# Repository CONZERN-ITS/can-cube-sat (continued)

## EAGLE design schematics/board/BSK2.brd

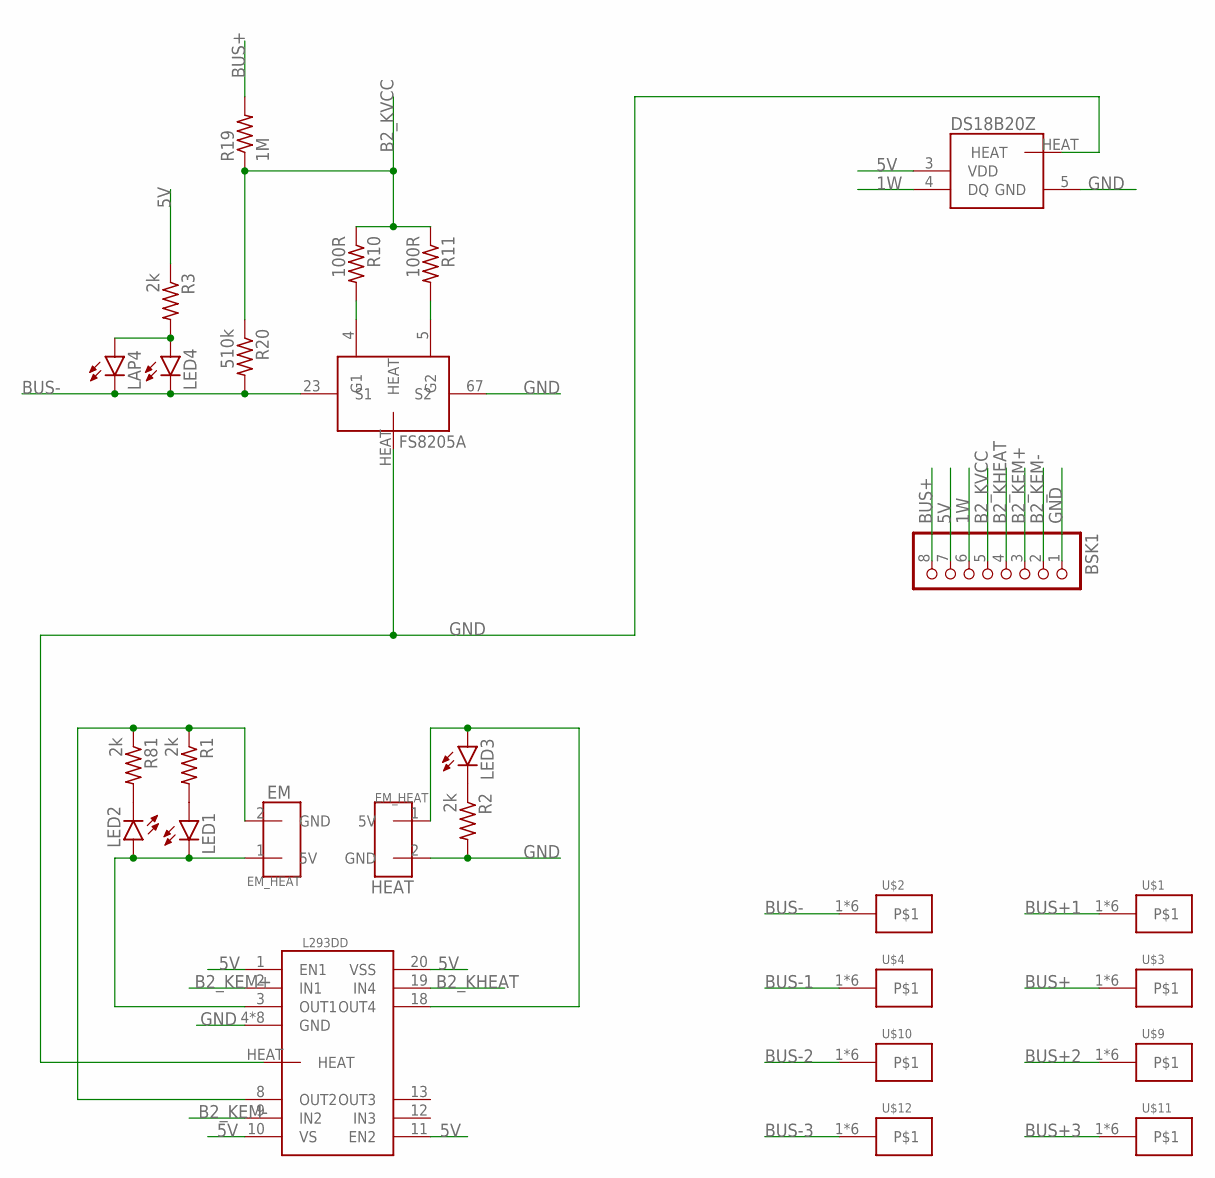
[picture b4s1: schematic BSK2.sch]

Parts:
BSK1: PINHD-1X8; 1X08
DS18B20Z: DS18B20Z
FS8205A: FS8205A+
L293DD: L293DD
LAP4: LAP4-BOTTOM; P47F-BOTTOM
LED1, LED2, LED3, LED4: LEDCHIPLED_0603; CHIPLED_0603
R1, R2, R3, R81: 2k; R0603
R10, R11: 100R; R0603
R19: 1M; R0603
R20: 510k; R0603
U$1, U$2, U$3, U$4, U$9, U$10, U$11, U$12: KCONNECT
U$6, U$7: EM_HEAT

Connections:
1W: BSK1.6, DS18B20Z.4 (DQ)
5V: BSK1.7, DS18B20Z.3 (VDD), L293DD.1 (EN1), L293DD.10 (VS), L293DD.11 (EN2), L293DD.20 (VSS), R3.1
B2_KEM+: BSK1.3, L293DD.2 (IN1)
B2_KEM-: BSK1.2, L293DD.9 (IN2)
B2_KHEAT: BSK1.4, L293DD.19 (IN4)
B2_KVCC: BSK1.5, R10.1, R11.1, R19.1, R20.1
BUS+: BSK1.8, R19.2, U$3.1, U$3.2, U$3.3, U$3.4, U$3.P$1, U$3.P$2
BUS+1: U$1.1, U$1.2, U$1.3, U$1.4, U$1.P$1, U$1.P$2
BUS+2: U$9.1, U$9.2, U$9.3, U$9.4, U$9.P$1, U$9.P$2
BUS+3: U$11.1, U$11.2, U$11.3, U$11.4, U$11.P$1, U$11.P$2
BUS-: FS8205A.23 (S1), LAP4.C, LED4.C, R20.2, U$2.1, U$2.2, U$2.3, U$2.4, U$2.P$1, U$2.P$2
BUS-1: U$4.1, U$4.2, U$4.3, U$4.4, U$4.P$1, U$4.P$2
BUS-2: U$10.1, U$10.2, U$10.3, U$10.4, U$10.P$1, U$10.P$2
BUS-3: U$12.1, U$12.2, U$12.3, U$12.4, U$12.P$1, U$12.P$2
GND: BSK1.1, DS18B20Z.5 (GND), DS18B20Z.HEAT, FS8205A.67 (S2), FS8205A.HEAT, L293DD.4 (GND), L293DD.5 (GND), L293DD.6 (GND), L293DD.7 (GND), L293DD.14 (GND), L293DD.15 (GND), L293DD.16 (GND), L293DD.17 (GND), L293DD.HEAT, R2.2, U$7.2 (GND)
unnamed: L293DD.3 (OUT1), LED1.C, LED2.A, U$6.1 (5V)
unnamed: L293DD.8 (OUT2), R1.1, R81.1, U$6.2 (GND)
unnamed: L293DD.18 (OUT4), LED3.A, U$7.1 (5V)
unnamed: FS8205A.4 (G1), R10.2
unnamed: FS8205A.5 (G2), R11.2
unnamed: LED2.C, R81.2
unnamed: LED1.A, R1.2
unnamed: LED3.C, R2.1
unnamed: LAP4.A, LED4.A, R3.2

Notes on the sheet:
HEAT

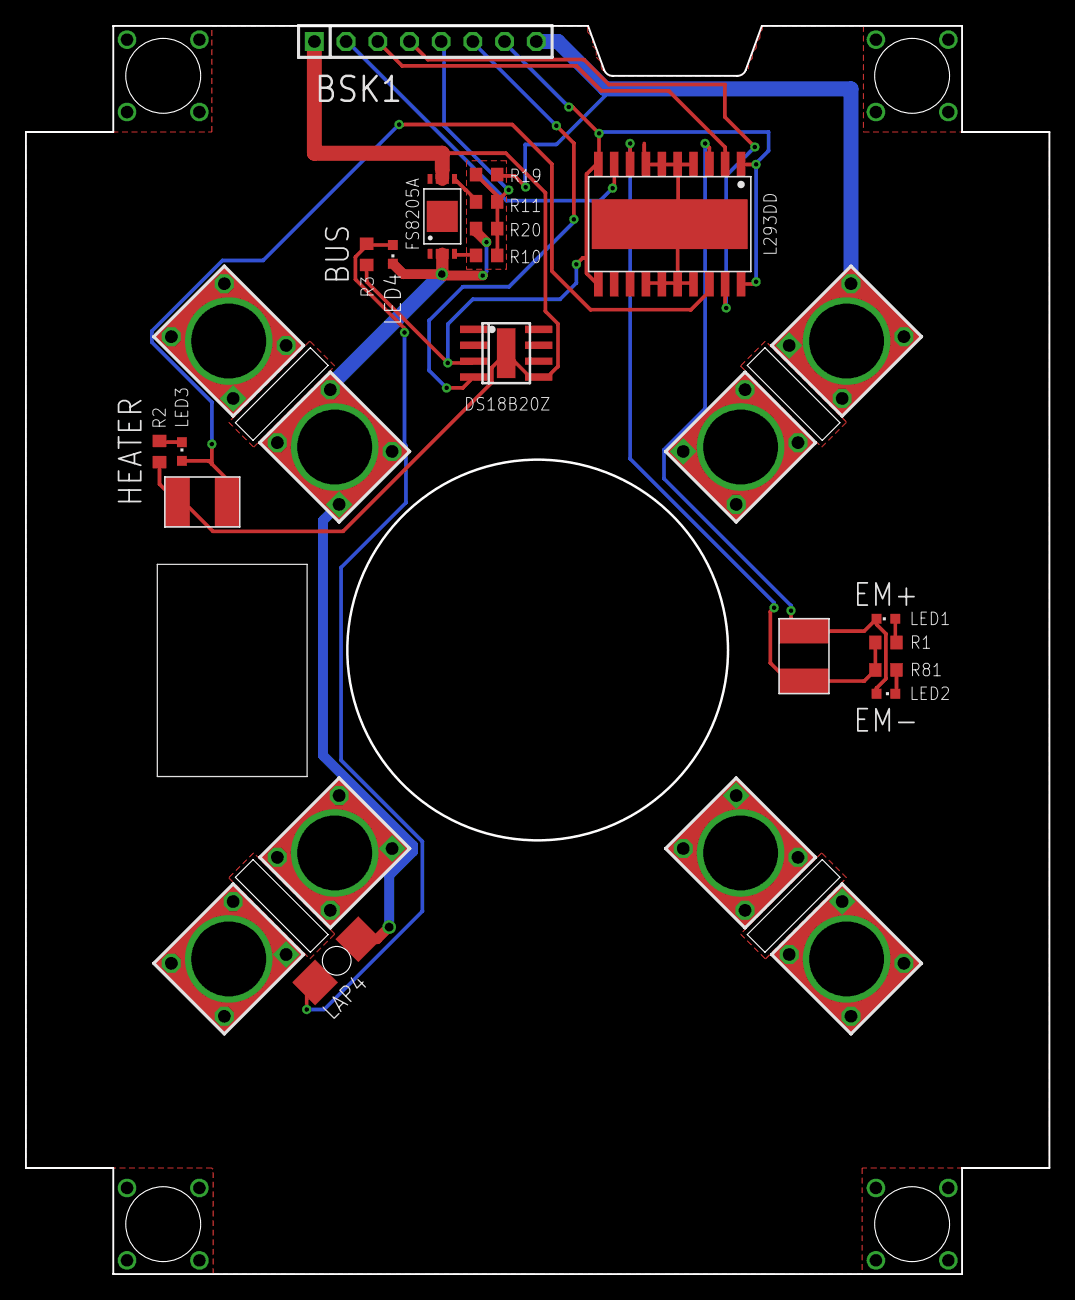
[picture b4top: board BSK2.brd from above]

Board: 2 copper layers, 82.0 x 100.0 mm, 27 parts (0 on the bottom side), 24 nets.

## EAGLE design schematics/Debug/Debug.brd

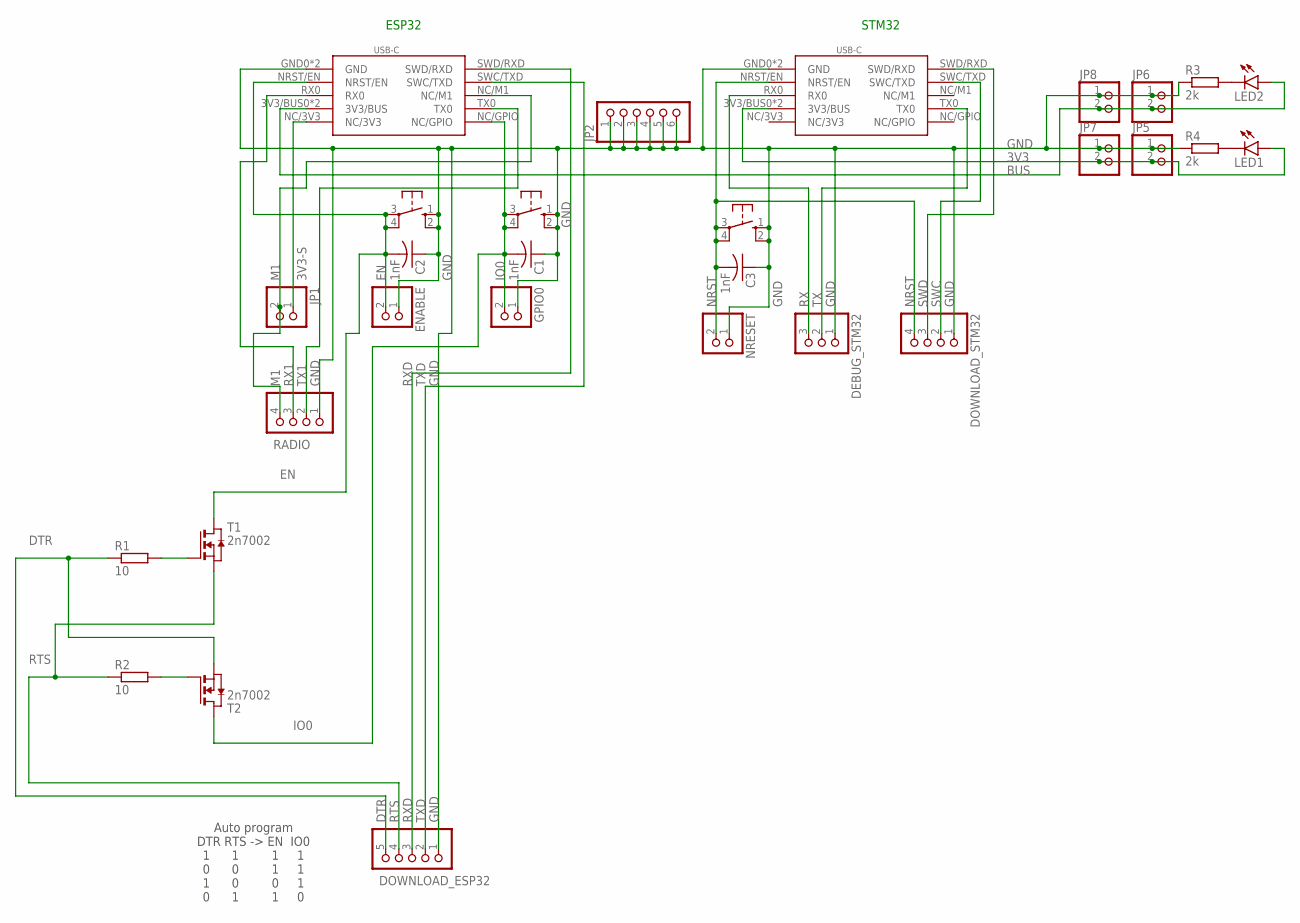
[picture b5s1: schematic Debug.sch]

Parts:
C1, C2, C3: 1nF; C0603
DEBUG_STM32: PINHD-1X3; 1X03
DOWNLOAD_ESP32: PINHD-1X5; 1X05
DOWNLOAD_STM32: PINHD-1X4; 1X04
EN: 10-XX; B3F-10XX
ENABLE: PINHD-1X2; 1X02
GPIO0: PINHD-1X2; 1X02
IO0: 10-XX; B3F-10XX
JP1, JP5, JP6, JP7, JP8: PINHD-1X2; 1X02
JP2: PINHD-1X6; 1X06
LED1, LED2: LEDCHIPLED_0603; CHIPLED_0603
NRESET: PINHD-1X2; 1X02
NRST: 10-XX; B3F-10XX
R1, R2: 10; R0603
R3, R4: 2k; R0603
RADIO: PINHD-1X4; 1X04
T1, T2: 2n7002; SOT-23
U$1, U$2: USB-C

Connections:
3V3: JP5.2, JP7.2, LED1.A, U$2.3V3/BUS0 (3V3/BUS), U$2.3V3/BUS1 (3V3/BUS)
3V3-S: JP1.1, U$1.NC/3V3
BUS: JP6.2, JP8.2, LED2.A, U$1.3V3/BUS0 (3V3/BUS), U$1.3V3/BUS1 (3V3/BUS)
DTR: DOWNLOAD_ESP32.5, R1.1, T2.2 (S)
EN: C2.2, EN.3, EN.4 (P1), ENABLE.2, T1.1 (D), U$1.NRST/EN
GND: C1.1, C2.1, C3.1, DEBUG_STM32.1, DOWNLOAD_ESP32.1, DOWNLOAD_STM32.1, EN.1 (S), EN.2 (S1), ENABLE.1, GPIO0.1, IO0.1 (S), IO0.2 (S1), JP2.1, JP2.2, JP2.3, JP2.4, JP2.5, JP2.6, JP5.1, JP6.1, JP7.1, JP8.1, NRESET.1, NRST.1 (S), NRST.2 (S1), R3.1, R4.1, RADIO.1, U$1.GND0 (GND), U$1.GND1 (GND), U$2.GND0 (GND), U$2.GND1 (GND)
IO0: C1.2, GPIO0.2, IO0.3, IO0.4 (P1), T2.1 (D), U$1.NC/GPIO
M1: JP1.2, RADIO.4, U$1.NC/M1
unnamed: R2.2, T2.3 (G)
unnamed: R1.2, T1.3 (G)
unnamed: LED1.C, R4.2
unnamed: LED2.C, R3.2
NRST: C3.2, DOWNLOAD_STM32.4, NRESET.2, NRST.3, NRST.4 (P1), U$2.NRST/EN
RTS: DOWNLOAD_ESP32.4, R2.1, T1.2 (S)
RX: DEBUG_STM32.3, U$2.RX0
RX1: RADIO.3, U$1.RX0
RXD: DOWNLOAD_ESP32.3, U$1.SWD/RXD
SWC: DOWNLOAD_STM32.2, U$2.SWC/TXD
SWD: DOWNLOAD_STM32.3, U$2.SWD/RXD
TX: DEBUG_STM32.2, U$2.TX0
TX1: RADIO.2, U$1.TX0
TXD: DOWNLOAD_ESP32.2, U$1.SWC/TXD

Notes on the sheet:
ESP32
STM32
Auto program DTR RTS -> EN IO0 1 1 1 1 0 0 1 1 1 0 0 1 0 1 1 0

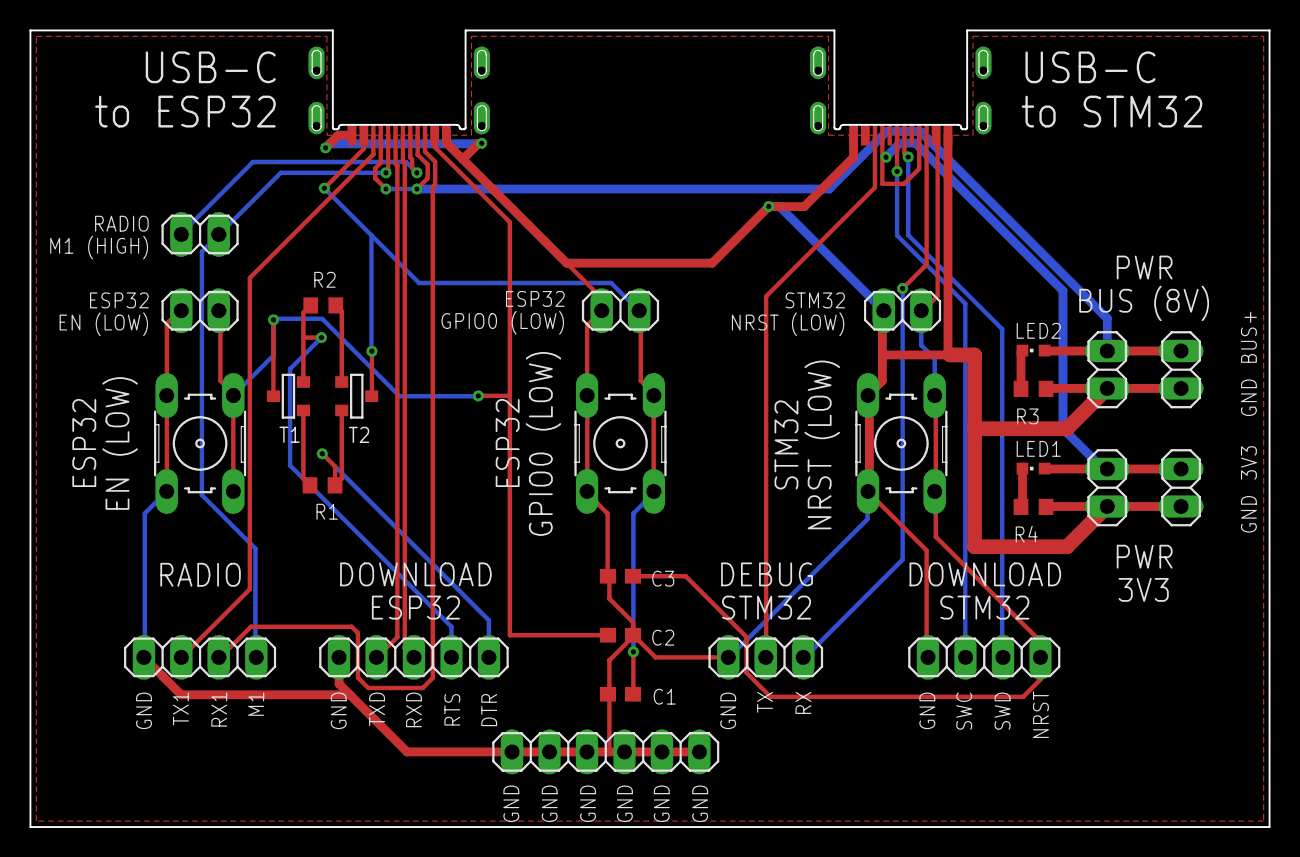
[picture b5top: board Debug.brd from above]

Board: 2 copper layers, 84.0 x 54.0 mm, 29 parts (0 on the bottom side), 22 nets.

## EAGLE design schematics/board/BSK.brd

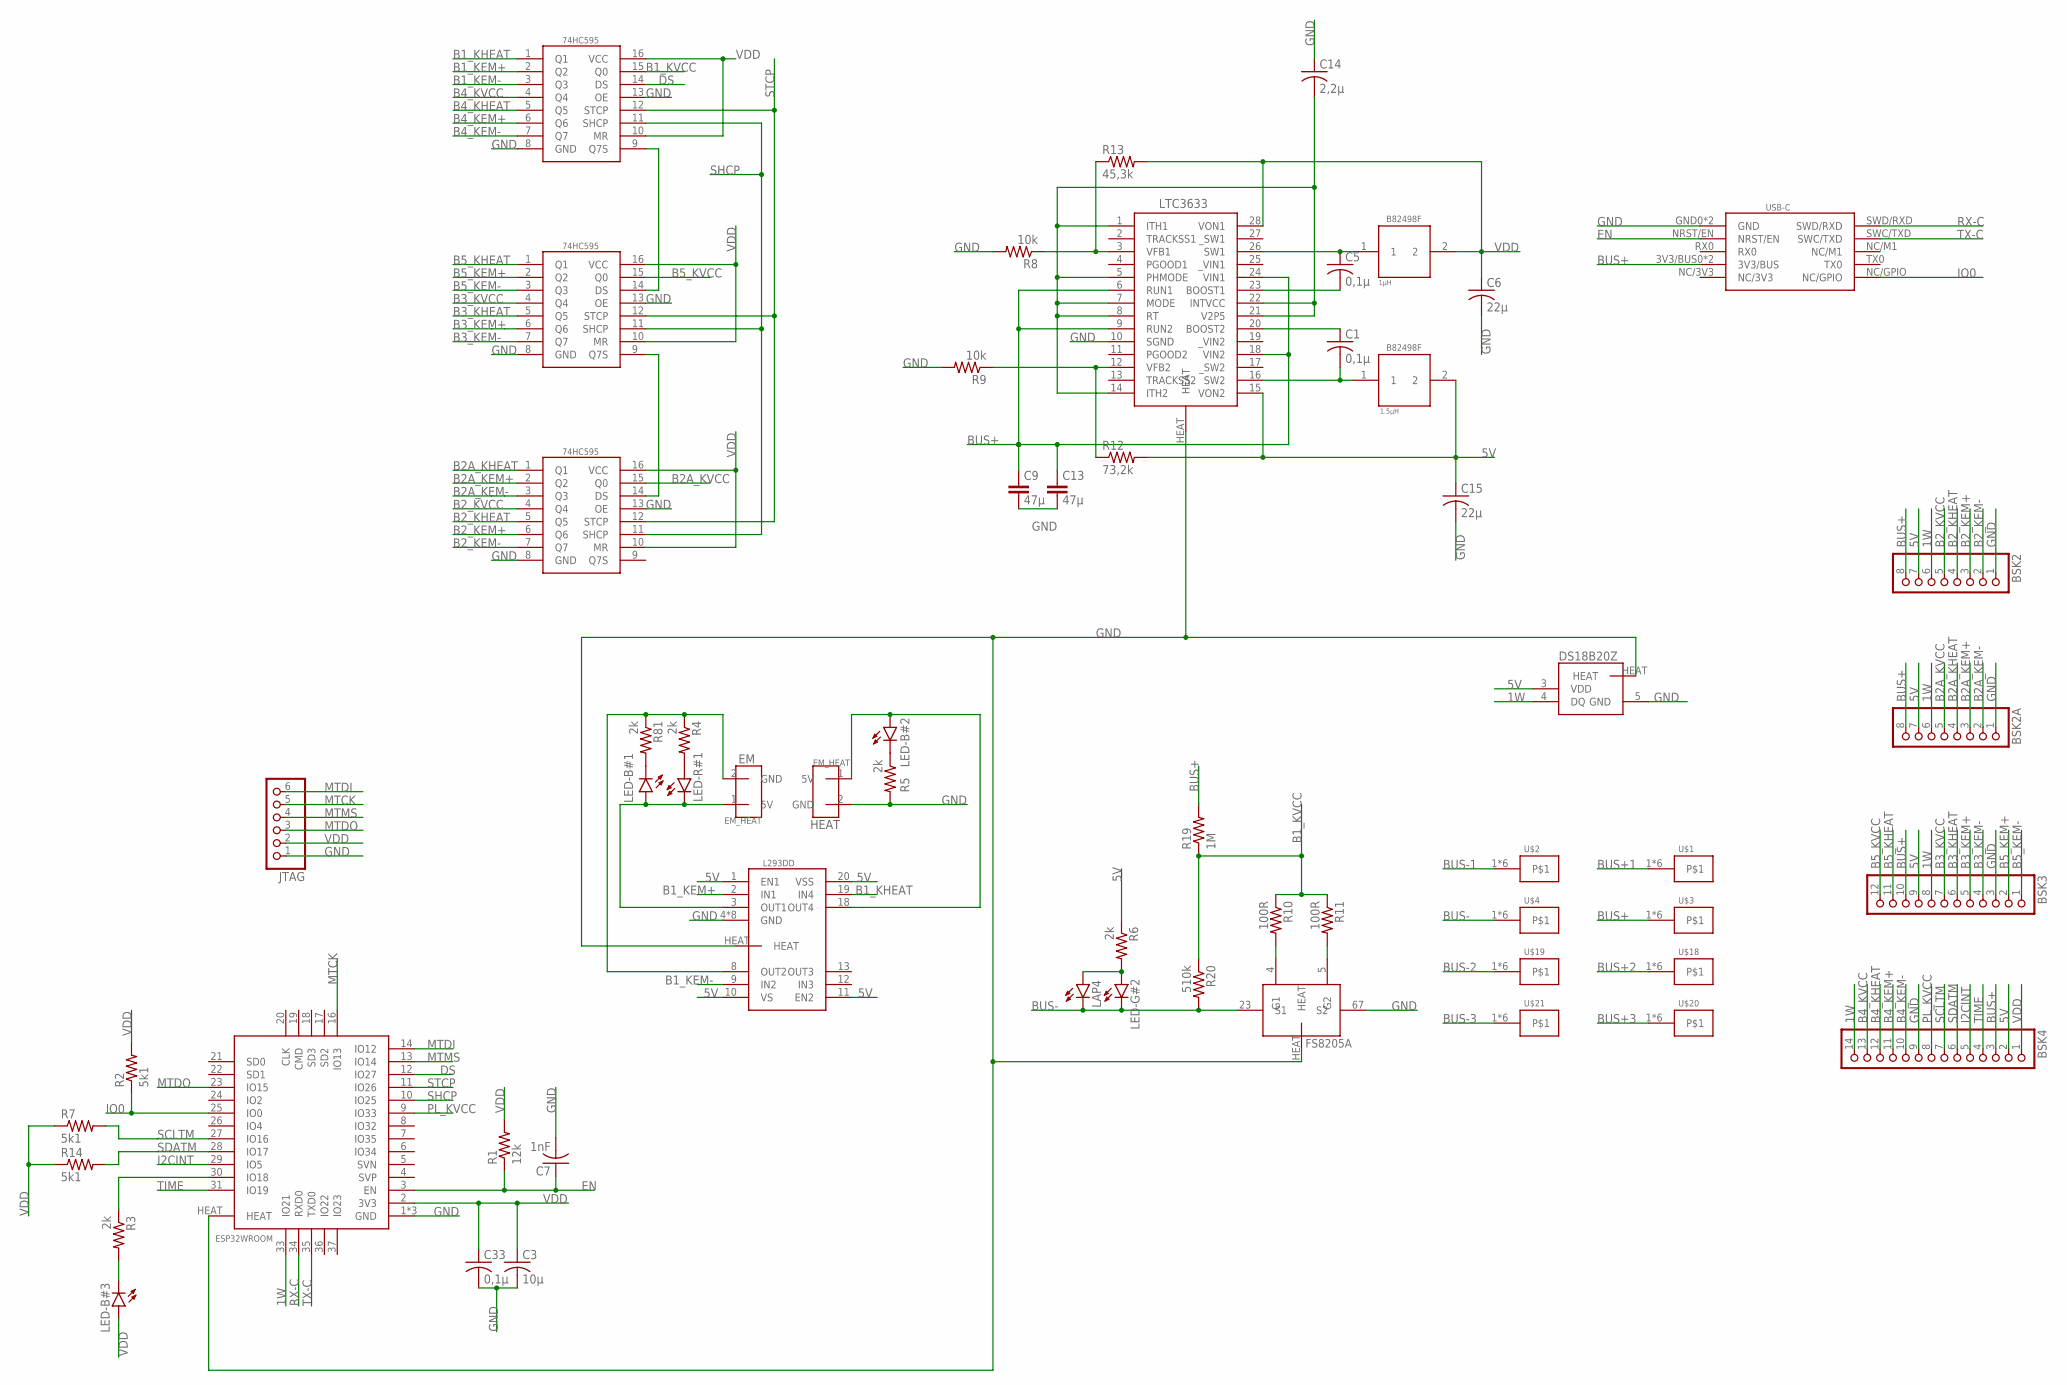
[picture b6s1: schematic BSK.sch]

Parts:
74HC595#1, 74HC595#2, 74HC595#3: 74HC595
B82498F#1: 1µH; B82498F
B82498F#2: B82498F
BSK2, BSK2A: PINHD-1X8; 1X08
BSK3: PINHD-1X12; 1X12
BSK4: PINHD-1X14; 1X14
C1, C5, C33: 0,1µ; C0603
C3: 10µ; C1206
C6, C15: 22µ; C1206
C7: 1nF; C0603
C9, C13: 47µ; C1210
C14: 2,2µ; C0603
DS18B20Z: DS18B20Z
EM: EM_HEAT
FS8205A: FS8205A+
HEATER: EM_HEAT
JTAG: PINHD-1X6; 1X06
L293DD: L293DD
LAP4: LAP4-BOTTOM; P47F-BOTTOM
LED-B#1, LED-B#2, LED-B#3: LEDCHIPLED_0603; CHIPLED_0603
LED-G#2: LEDCHIPLED_0603; CHIPLED_0603
LED-R#1: LEDCHIPLED_0603; CHIPLED_0603
LTC3633: LTC3633
R1: 12k; R0603
R2, R7, R14: 5k1; R0603
R3, R4, R5, R6, R81: 2k; R0603
R8, R9: 10k; R0603
R10, R11: 100R; R0603
R12: 73,2k; R0603
R13: 45,3k; R0603
R19: 1M; R0603
R20: 510k; R0603
U$1, U$2, U$3, U$4, U$18, U$19, U$20, U$21: KCONNECT
U$13: ESP32WROOM
USB-C: USB-C

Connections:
1W: BSK2.6, BSK2A.6, BSK3.8, BSK4.14, DS18B20Z.4 (DQ), U$13.33 (IO21)
5V: B82498F#2.2, BSK2.7, BSK2A.7, BSK3.9, BSK4.2, C15.1, DS18B20Z.3 (VDD), L293DD.1 (EN1), L293DD.10 (VS), L293DD.11 (EN2), L293DD.20 (VSS), LTC3633.15 (VON2), R6.1, R12.2
B1_KEM+: 74HC595#1.2 (Q2), L293DD.2 (IN1)
B1_KEM-: 74HC595#1.3 (Q3), L293DD.9 (IN2)
B1_KHEAT: 74HC595#1.1 (Q1), L293DD.19 (IN4)
B1_KVCC: 74HC595#1.15 (Q0), R10.1, R11.1, R19.1, R20.1
B2A_KEM+: 74HC595#3.2 (Q2), BSK2A.3
B2A_KEM-: 74HC595#3.3 (Q3), BSK2A.2
B2A_KHEAT: 74HC595#3.1 (Q1), BSK2A.4
B2A_KVCC: 74HC595#3.15 (Q0), BSK2A.5
B2_KEM+: 74HC595#3.6 (Q6), BSK2.3
B2_KEM-: 74HC595#3.7 (Q7), BSK2.2
B2_KHEAT: 74HC595#3.5 (Q5), BSK2.4
B2_KVCC: 74HC595#3.4 (Q4), BSK2.5
B3_KEM+: 74HC595#2.6 (Q6), BSK3.5
B3_KEM-: 74HC595#2.7 (Q7), BSK3.4
B3_KHEAT: 74HC595#2.5 (Q5), BSK3.6
B3_KVCC: 74HC595#2.4 (Q4), BSK3.7
B4_KEM+: 74HC595#1.6 (Q6), BSK4.11
B4_KEM-: 74HC595#1.7 (Q7), BSK4.10
B4_KHEAT: 74HC595#1.5 (Q5), BSK4.12
B4_KVCC: 74HC595#1.4 (Q4), BSK4.13
B5_KEM+: 74HC595#2.2 (Q2), BSK3.2
B5_KEM-: 74HC595#2.3 (Q3), BSK3.1
B5_KHEAT: 74HC595#2.1 (Q1), BSK3.11
B5_KVCC: 74HC595#2.15 (Q0), BSK3.12
BUS+: BSK2.8, BSK2A.8, BSK3.10, BSK4.3, C9.1, C13.1, LTC3633.6 (RUN1), LTC3633.9 (RUN2), LTC3633.18 (VIN2), LTC3633.24 (VIN1), R19.2, U$3.1, U$3.2, U$3.3, U$3.4, U$3.P$1, U$3.P$2, USB-C.3V3/BUS0 (3V3/BUS), USB-C.3V3/BUS1 (3V3/BUS)
BUS+1: U$1.1, U$1.2, U$1.3, U$1.4, U$1.P$1, U$1.P$2
BUS+2: U$18.1, U$18.2, U$18.3, U$18.4, U$18.P$1, U$18.P$2
BUS+3: U$20.1, U$20.2, U$20.3, U$20.4, U$20.P$1, U$20.P$2
BUS-: FS8205A.23 (S1), LAP4.C, LED-G#2.C, R20.2, U$4.1, U$4.2, U$4.3, U$4.4, U$4.P$1, U$4.P$2
BUS-1: U$2.1, U$2.2, U$2.3, U$2.4, U$2.P$1, U$2.P$2
BUS-2: U$19.1, U$19.2, U$19.3, U$19.4, U$19.P$1, U$19.P$2
BUS-3: U$21.1, U$21.2, U$21.3, U$21.4, U$21.P$1, U$21.P$2
DS: 74HC595#1.14 (DS), U$13.12 (IO27)
EN: C7.1, R1.1, U$13.3 (EN), USB-C.NRST/EN
GND: 74HC595#1.8 (GND), 74HC595#1.13 (OE), 74HC595#2.8 (GND), 74HC595#2.13 (OE), 74HC595#3.8 (GND), 74HC595#3.13 (OE), BSK2.1, BSK2A.1, BSK3.3, BSK4.9, C3.2, C6.2, C7.2, C9.2, C13.2, C14.1, C15.2, C33.2, DS18B20Z.5 (GND), DS18B20Z.HEAT, FS8205A.67 (S2), FS8205A.HEAT, HEATER.2 (GND), JTAG.1, L293DD.4 (GND), L293DD.5 (GND), L293DD.6 (GND), L293DD.7 (GND), L293DD.14 (GND), L293DD.15 (GND), L293DD.16 (GND), L293DD.17 (GND), L293DD.HEAT, LTC3633.10 (SGND), LTC3633.HEAT, R5.2, R8.2, R9.2, U$13.1 (GND), U$13.15 (GND), U$13.38 (GND), U$13.HEAT, USB-C.GND0 (GND), USB-C.GND1 (GND)
I2CINT: BSK4.5, U$13.29 (IO5)
IO0: R2.1, U$13.25 (IO0), USB-C.NC/GPIO
IO1: R3.1, U$13.30 (IO18)
MTCK: JTAG.5, U$13.16 (IO13)
MTDI: JTAG.6, U$13.14 (IO12)
MTDO: JTAG.3, U$13.23 (IO15)
MTMS: JTAG.4, U$13.13 (IO14)
unnamed: EM.1 (5V), L293DD.3 (OUT1), LED-B#1.A, LED-R#1.C
unnamed: EM.2 (GND), L293DD.8 (OUT2), R4.1, R81.1
unnamed: HEATER.1 (5V), L293DD.18 (OUT4), LED-B#2.A
unnamed: FS8205A.4 (G1), R10.2
unnamed: FS8205A.5 (G2), R11.2
unnamed: 74HC595#1.9 (Q7S), 74HC595#2.14 (DS)
unnamed: 74HC595#2.9 (Q7S), 74HC595#3.14 (DS)
unnamed: C14.2, LTC3633.1 (ITH1), LTC3633.5 (PHMODE), LTC3633.7 (MODE), LTC3633.8 (RT), LTC3633.14 (ITH2), LTC3633.21 (V2P5), LTC3633.22 (INTVCC)
unnamed: LTC3633.3 (VFB1), R8.1, R13.1
unnamed: B82498F#1.1, C5.1, LTC3633.26 (SW1)
unnamed: C5.2, LTC3633.23 (BOOST1)
unnamed: C1.1, LTC3633.20 (BOOST2)
unnamed: B82498F#2.1, C1.2, LTC3633.16 (SW2)
unnamed: LED-B#3.C, R3.2
unnamed: LED-B#1.C, R81.2
unnamed: LED-R#1.A, R4.2
unnamed: LED-B#2.C, R5.1
unnamed: LAP4.A, LED-G#2.A, R6.2
unnamed: LTC3633.12 (VFB2), R9.1, R12.1
PL_KVCC: BSK4.8, U$13.9 (IO33)
RX-C: U$13.34 (RXD0), USB-C.SWD/RXD
SCLTM: BSK4.7, R7.2, U$13.27 (IO16)
SDATM: BSK4.6, R14.2, U$13.28 (IO17)
SHCP: 74HC595#1.11 (SHCP), 74HC595#2.11 (SHCP), 74HC595#3.11 (SHCP), U$13.10 (IO25)
STCP: 74HC595#1.12 (STCP), 74HC595#2.12 (STCP), 74HC595#3.12 (STCP), U$13.11 (IO26)
TIME: BSK4.4, U$13.31 (IO19)
TX-C: U$13.35 (TXD0), USB-C.SWC/TXD
VDD: 74HC595#1.10 (MR), 74HC595#1.16 (VCC), 74HC595#2.10 (MR), 74HC595#2.16 (VCC), 74HC595#3.10 (MR), 74HC595#3.16 (VCC), B82498F#1.2, BSK4.1, C3.1, C6.1, C33.1, JTAG.2, LED-B#3.A, LTC3633.28 (VON1), R1.2, R2.2, R7.1, R13.2, R14.1, U$13.2 (3V3)

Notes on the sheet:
HEAT
1µH
1.5µH

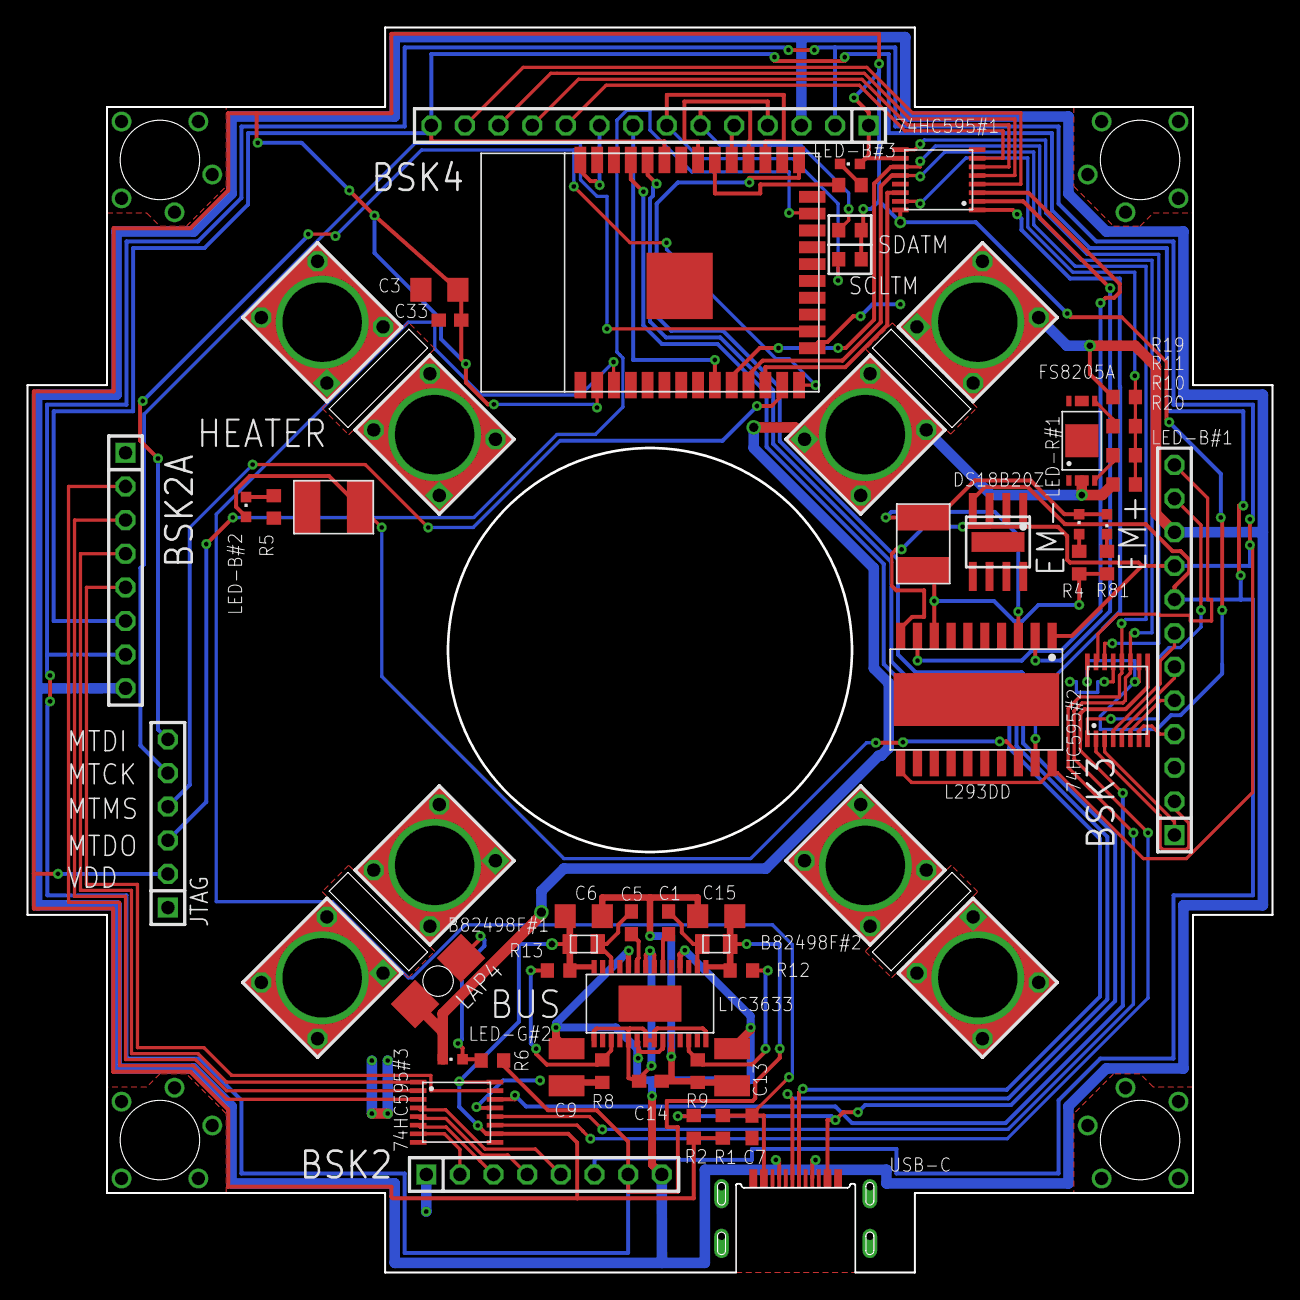
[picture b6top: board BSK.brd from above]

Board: 2 copper layers, 94.0 x 94.0 mm, 59 parts (0 on the bottom side), 72 nets.

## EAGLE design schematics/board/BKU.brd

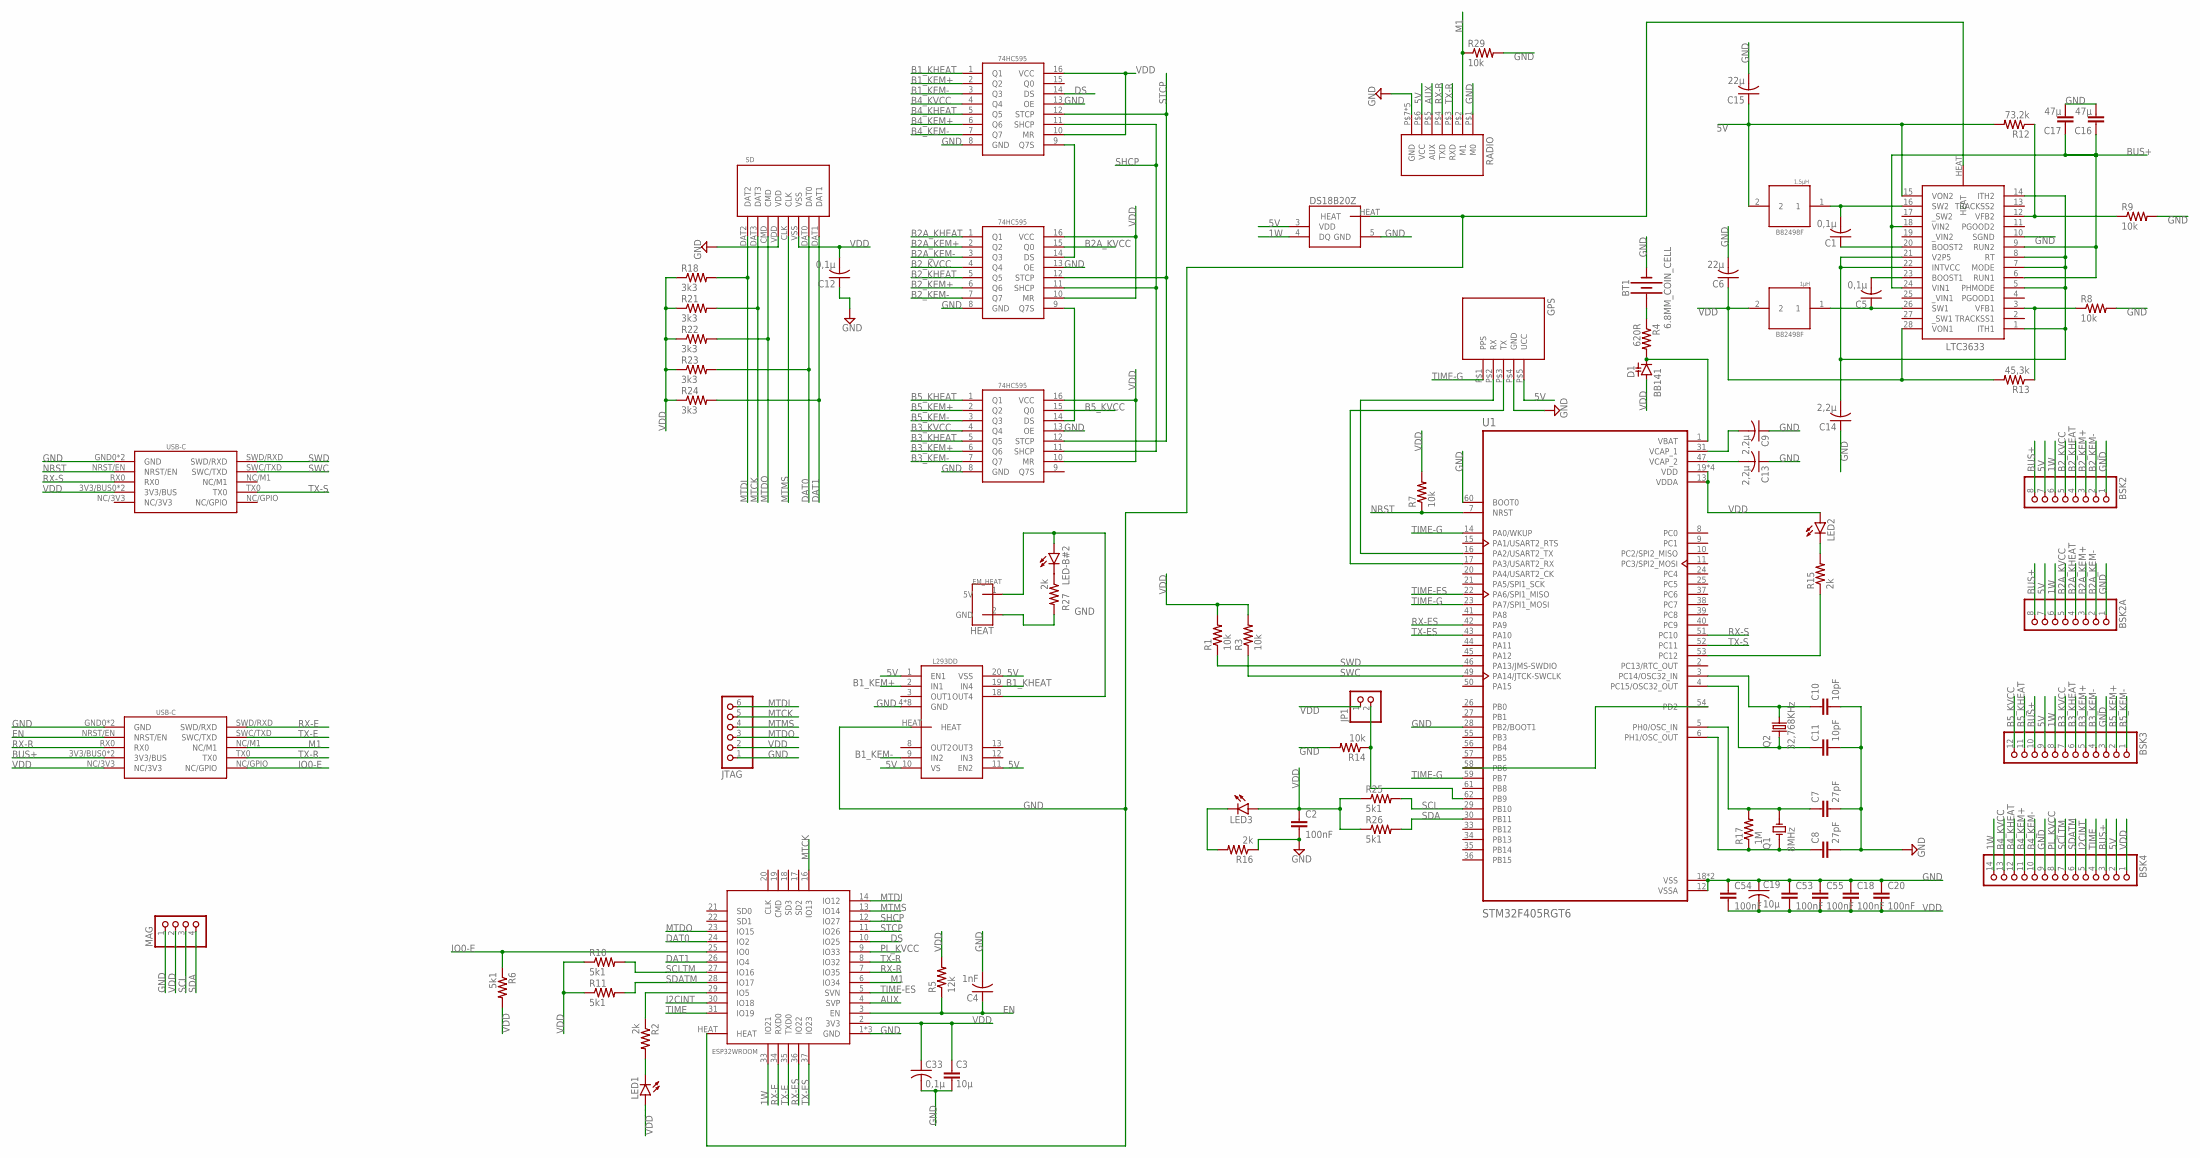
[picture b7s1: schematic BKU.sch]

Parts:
BSK2, BSK2A: PINHD-1X8; 1X08
BSK3: PINHD-1X12; 1X12
BSK4: PINHD-1X14; 1X14
BT1: 6.8MM_COIN_CELL; BATTCON-6.8MM
C1, C5, C12, C33: 0,1µ; C0603
C2, C18, C20, C53, C54, C55: 100nF; C0603
C3, C19: 10µ; C1206
C4: 1nF; C0603
C6, C15: 22µ; C1206
C7, C8: 27pF; C0603
C9, C13, C14: 2,2µ; C0603
C10, C11: 10pF; C0603
C16, C17: 47µ; C1210
D1: BB141; SOD523
GPS: GPSNEO6M; GPS-NEO6M
JP1: PINHD-1X2; 1X02
JTAG: PINHD-1X6; 1X06
LED1, LED2, LED3: LEDCHIPLED_0603; CHIPLED_0603
LED-B#2: LEDCHIPLED_0603; CHIPLED_0603
MAG: PINHD-1X4; 1X04
Q1: 8MHz; XTAL_9C-8.000MEEJ-T
Q2: 32,768KHz; C005R
R1, R3, R7, R8, R9, R14, R29: 10k; R0603
R2, R15, R16, R27: 2k; R0603
R4: 620R; R0603
R5: 12k; R0603
R6, R10, R11, R25, R26: 5k1; R0603
R12: 73,2k; R0603
R13: 45,3k; R0603
R17: 1M; R0603
R18, R21, R22, R23, R24: 3k3; R0603
RADIO: RADIO
SD: SD
U1: STM32F405RGT6; QFP50P1200X1200X160-64N
U$4, U$6: USB-C
U$5: DS18B20Z
U$7: EM_HEAT
U$8: L293DD
U$10: LTC3633
U$11: 1µH; B82498F
U$12: B82498F
U$13: ESP32WROOM
U$18, U$19, U$20: 74HC595

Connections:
1W: BSK2.6, BSK2A.6, BSK3.8, BSK4.14, U$5.4 (DQ), U$13.33 (IO21)
5V: BSK2.7, BSK2A.7, BSK3.9, BSK4.2, C15.1, GPS.P$5 (UCC), R12.2, RADIO.P$6 (VCC), U$5.3 (VDD), U$8.1 (EN1), U$8.10 (VS), U$8.11 (EN2), U$8.20 (VSS), U$10.15 (VON2), U$12.2
AUX: RADIO.P$5 (AUX), U$13.4 (SVP)
B1_KEM+: U$8.2 (IN1), U$18.2 (Q2)
B1_KEM-: U$8.9 (IN2), U$18.3 (Q3)
B1_KHEAT: U$8.19 (IN4), U$18.1 (Q1)
B2A_KEM+: BSK2A.3, U$19.2 (Q2)
B2A_KEM-: BSK2A.2, U$19.3 (Q3)
B2A_KHEAT: BSK2A.4, U$19.1 (Q1)
B2A_KVCC: BSK2A.5, U$19.15 (Q0)
B2_KEM+: BSK2.3, U$19.6 (Q6)
B2_KEM-: BSK2.2, U$19.7 (Q7)
B2_KHEAT: BSK2.4, U$19.5 (Q5)
B2_KVCC: BSK2.5, U$19.4 (Q4)
B3_KEM+: BSK3.5, U$20.6 (Q6)
B3_KEM-: BSK3.4, U$20.7 (Q7)
B3_KHEAT: BSK3.6, U$20.5 (Q5)
B3_KVCC: BSK3.7, U$20.4 (Q4)
B4_KEM+: BSK4.11, U$18.6 (Q6)
B4_KEM-: BSK4.10, U$18.7 (Q7)
B4_KHEAT: BSK4.12, U$18.5 (Q5)
B4_KVCC: BSK4.13, U$18.4 (Q4)
B5_KEM+: BSK3.2, U$20.2 (Q2)
B5_KEM-: BSK3.1, U$20.3 (Q3)
B5_KHEAT: BSK3.11, U$20.1 (Q1)
B5_KVCC: BSK3.12, U$20.15 (Q0)
BUS+: BSK2.8, BSK2A.8, BSK3.10, BSK4.3, C16.1, C17.1, U$6.3V3/BUS0 (3V3/BUS), U$6.3V3/BUS1 (3V3/BUS), U$10.6 (RUN1), U$10.9 (RUN2), U$10.18 (VIN2), U$10.24 (VIN1)
DAT0: R23.2, SD.DAT0, U$13.24 (IO2)
DAT1: R24.2, SD.DAT1, U$13.26 (IO4)
DS: U$13.10 (IO25), U$18.14 (DS)
EN: C4.1, R5.1, U$6.NRST/EN, U$13.3 (EN)
GND: BSK2.1, BSK2A.1, BSK3.3, BSK4.9, BT1.-, C2.2, C3.2, C4.2, C6.2, C7.2, C8.2, C9.1, C10.2, C11.2, C12.1, C13.1, C14.1, C15.2, C16.2, C17.2, C18.1, C19.1, C20.1, C33.2, C53.1, C54.1, C55.1, GPS.P$4 (GND), JTAG.1, MAG.1, R8.2, R9.2, R14.2, R16.1, R27.2, R29.2, RADIO.P$1 (M0), RADIO.P$7 (GND), RADIO.P$9 (GND), RADIO.P$15 (GND), RADIO.P$16 (GND), RADIO.P$17 (GND), SD.VDD, U1.12 (VSSA), U1.18 (VSS), U1.28 (PB2/BOOT1), U1.60 (BOOT0), U1.63 (VSS), U$4.GND0 (GND), U$4.GND1 (GND), U$5.5 (GND), U$5.HEAT, U$6.GND0 (GND), U$6.GND1 (GND), U$7.2 (GND), U$8.4 (GND), U$8.5 (GND), U$8.6 (GND), U$8.7 (GND), U$8.14 (GND), U$8.15 (GND), U$8.16 (GND), U$8.17 (GND), U$8.HEAT, U$10.10 (SGND), U$10.HEAT, U$13.1 (GND), U$13.15 (GND), U$13.38 (GND), U$13.HEAT, U$18.8 (GND), U$18.13 (OE), U$19.8 (GND), U$19.13 (OE), U$20.8 (GND), U$20.13 (OE)
I2CINT: BSK4.5, U$13.30 (IO18)
IO0-E: R6.1, U$6.NC/GPIO, U$13.25 (IO0)
IO1: R2.1, U$13.29 (IO5)
M1: R29.1, RADIO.P$2 (M1), U$6.NC/M1, U$13.6 (IO34)
MTCK: JTAG.5, R21.2, SD.DAT3, U$13.16 (IO13)
MTDI: JTAG.6, R18.2, SD.DAT2, U$13.14 (IO12)
MTDO: JTAG.3, R22.2, SD.CMD, U$13.23 (IO15)
MTMS: JTAG.4, SD.CLK, U$13.13 (IO14)
unnamed: BT1.+, R4.1
unnamed: D1.C, R4.2, U1.1 (VBAT)
unnamed: LED-B#2.A, U$7.1 (5V), U$8.18 (OUT4)
unnamed: LED1.C, R2.2
unnamed: JP1.2, R14.1, U1.62 (PB9)
unnamed: U1.54 (PD2), U1.58 (PB6)
unnamed: C9.2, U1.31 (VCAP_1)
unnamed: C13.2, U1.47 (VCAP_2)
unnamed: C8.1, Q1.1, R17.1, U1.6 (PH1/OSC_OUT)
unnamed: U$18.9 (Q7S), U$19.14 (DS)
unnamed: U$19.9 (Q7S), U$20.14 (DS)
unnamed: C14.2, U$10.1 (ITH1), U$10.5 (PHMODE), U$10.7 (MODE), U$10.8 (RT), U$10.14 (ITH2), U$10.21 (V2P5), U$10.22 (INTVCC)
unnamed: R8.1, R13.1, U$10.3 (VFB1)
unnamed: C5.1, U$10.26 (SW1), U$11.1
unnamed: C7.1, Q1.2, R17.2, U1.5 (PH0/OSC_IN)
unnamed: C5.2, U$10.23 (BOOST1)
unnamed: C1.1, U$10.20 (BOOST2)
unnamed: C1.2, U$10.16 (SW2), U$12.1
unnamed: C10.1, Q2.P$2 (2), U1.3 (PC14/OSC32_IN)
unnamed: C11.1, Q2.P$1 (1), U1.4 (PC15/OSC32_OUT)
unnamed: LED2.C, R15.2
unnamed: R15.1, U1.53 (PC12)
unnamed: R9.1, R12.1, U$10.12 (VFB2)
unnamed: LED3.C, R16.2
unnamed: GPS.P$2 (RX), U1.16 (PA2/USART2_TX)
unnamed: GPS.P$3 (TX), U1.17 (PA3/USART2_RX)
unnamed: LED-B#2.C, R27.1
NRST: R7.1, U1.7 (NRST), U$4.NRST/EN
PL_KVCC: BSK4.8, U$13.9 (IO33)
RX-E: U$6.SWD/RXD, U$13.34 (RXD0)
RX-ES: U1.42 (PA9), U$13.36 (IO22)
RX-R: RADIO.P$4 (TXD), U$6.RX0, U$13.7 (IO35)
RX-S: U1.51 (PC10), U$4.RX0
SCL: MAG.3, R25.2, U1.29 (PB10)
SCLTM: BSK4.7, R10.2, U$13.27 (IO16)
SDA: MAG.4, R26.2, U1.30 (PB11)
SDATM: BSK4.6, R11.2, U$13.28 (IO17)
SHCP: U$13.12 (IO27), U$18.11 (SHCP), U$19.11 (SHCP), U$20.11 (SHCP)
STCP: U$13.11 (IO26), U$18.12 (STCP), U$19.12 (STCP), U$20.12 (STCP)
SWC: R3.1, U1.49 (PA14/JTCK-SWCLK), U$4.SWC/TXD
SWD: R1.1, U1.46 (PA13/JMS-SWDIO), U$4.SWD/RXD
TIME: BSK4.4, U$13.31 (IO19)
TIME-ES: U1.22 (PA6/SPI1_MISO), U$13.5 (SVN)
TIME-G: GPS.P$1 (PPS), U1.14 (PA0/WKUP), U1.23 (PA7/SPI1_MOSI), U1.59 (PB7)
TX-E: U$6.SWC/TXD, U$13.35 (TXD0)
TX-ES: U1.43 (PA10), U$13.37 (IO23)
TX-R: RADIO.P$3 (RXD), U$6.TX0, U$13.8 (IO32)
TX-S: U1.52 (PC11), U$4.TX0
VDD: BSK4.1, C2.1, C3.1, C6.1, C12.2, C18.2, C19.2, C20.2, C33.1, C53.2, C54.2, C55.2, D1.A, JP1.1, JTAG.2, LED1.A, LED2.A, LED3.A, MAG.2, R1.2, R3.2, R5.2, R6.2, R7.2, R10.1, R11.1, R13.2, R18.1, R21.1, R22.1, R23.1, R24.1, R25.1, R26.1, SD.VSS, U1.13 (VDDA), U1.19 (VDD), U1.32 (VDD), U1.48 (VDD), U1.64 (VDD), U$4.3V3/BUS0 (3V3/BUS), U$4.3V3/BUS1 (3V3/BUS), U$6.NC/3V3, U$10.28 (VON1), U$11.2, U$13.2 (3V3), U$18.10 (MR), U$18.16 (VCC), U$19.10 (MR), U$19.16 (VCC), U$20.10 (MR), U$20.16 (VCC)

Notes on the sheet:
HEAT
1µH
1.5µH

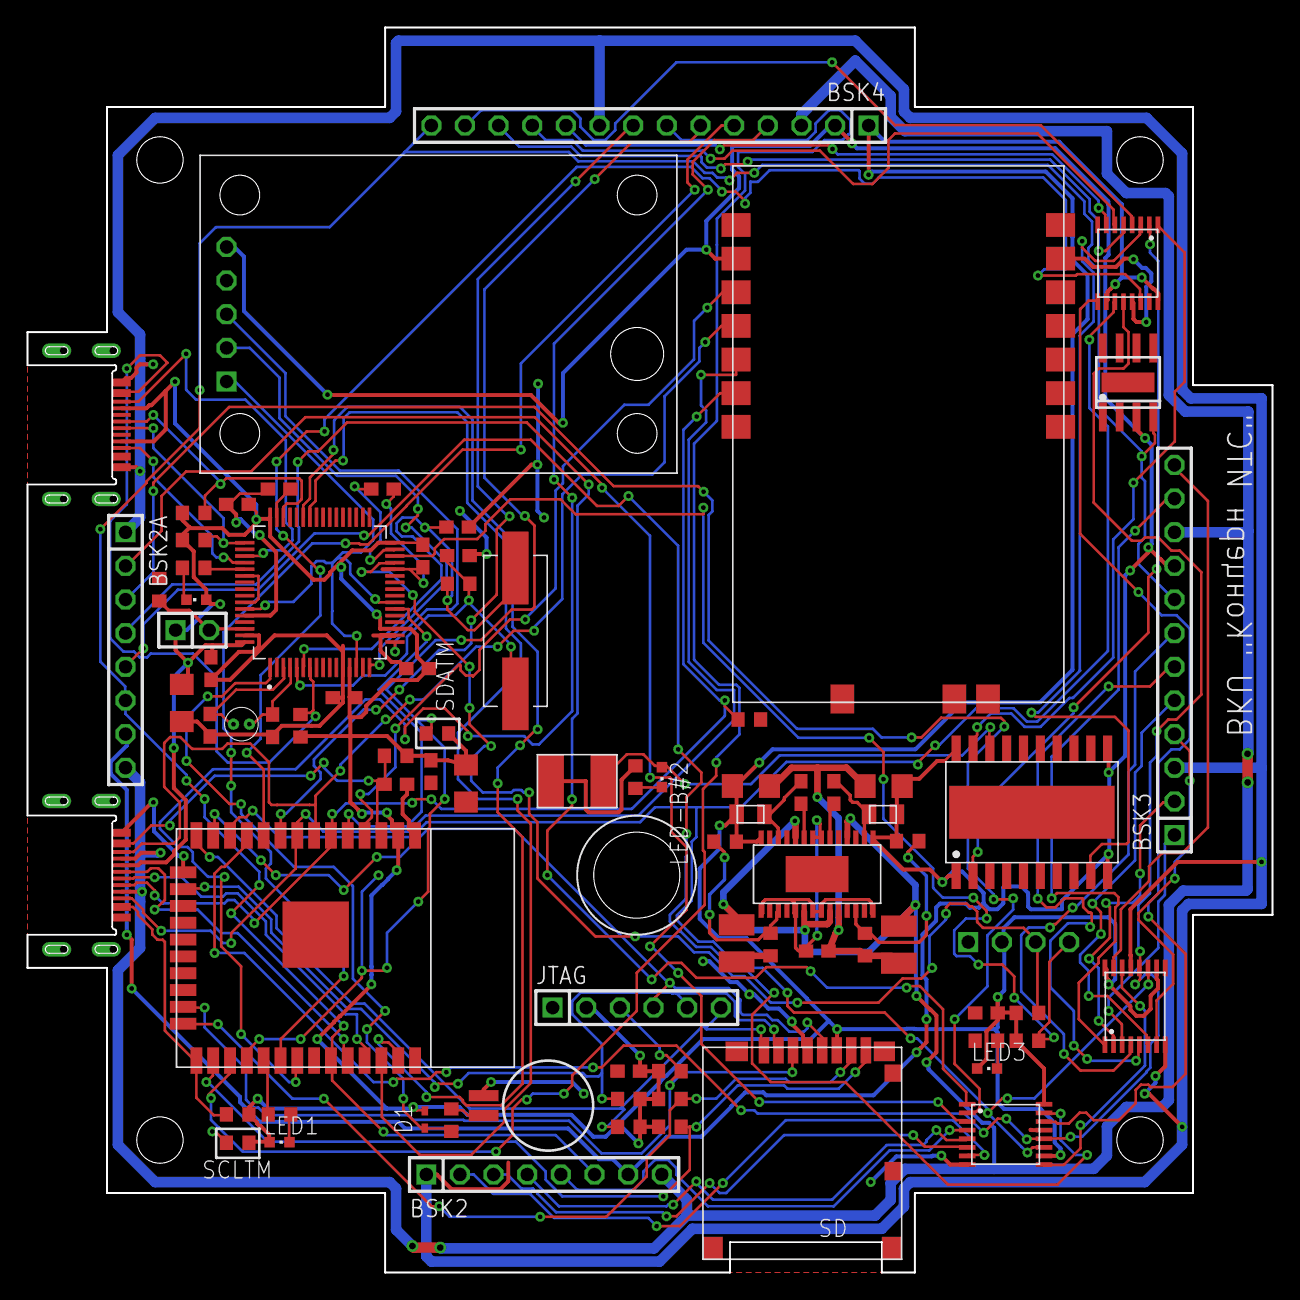
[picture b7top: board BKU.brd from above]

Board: 2 copper layers, 94.0 x 94.0 mm, 81 parts (1 on the bottom side), 89 nets.
